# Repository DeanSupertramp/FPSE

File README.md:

# FPSE
Repository per il corso di Fondamenti di Programmazione dei Sistemi Embedded 2020/2021

## Info generali
Su questa repository vengono riportate tutte le attività svolte durante il corso. I progetti/codici prodotti sono stati sviluppati in **STM32CubeIDE**. La scheda di sviluppo utilizzata è la **STM32 Nucleo-F446RE**. Viene inoltre riportato il progetto di fine corso proposto, ovvero un _Self Balancing Robot_.

## Indice degli argomenti
1. [Attività 1 - STM32 Programmazione Base](https://github.com/DeanSupertramp/FPSE/tree/main/Attivit%C3%A01)    
2. [Attività 2 - Digital IO e GPIO](https://github.com/DeanSupertramp/FPSE/tree/main/Attivit%C3%A02) 
3. [Attività 3 - GPIO e Interrupt](https://github.com/DeanSupertramp/FPSE/tree/main/Attivit%C3%A03) 
4. [Attività 4 - IO Analogico](https://github.com/DeanSupertramp/FPSE/tree/main/Attivit%C3%A04) 
5. [Attività 5 - Timers e PWM](https://github.com/DeanSupertramp/FPSE/tree/main/Attivit%C3%A05) 
6. [Attività 6 - Comunicazione Seriale](https://github.com/DeanSupertramp/FPSE/tree/main/Attivit%C3%A06) 
7. [Progetto - Self Balancing Robot](https://github.com/DeanSupertramp/FPSE/tree/main/Progetto) 

<!-- * [License](#license) -->

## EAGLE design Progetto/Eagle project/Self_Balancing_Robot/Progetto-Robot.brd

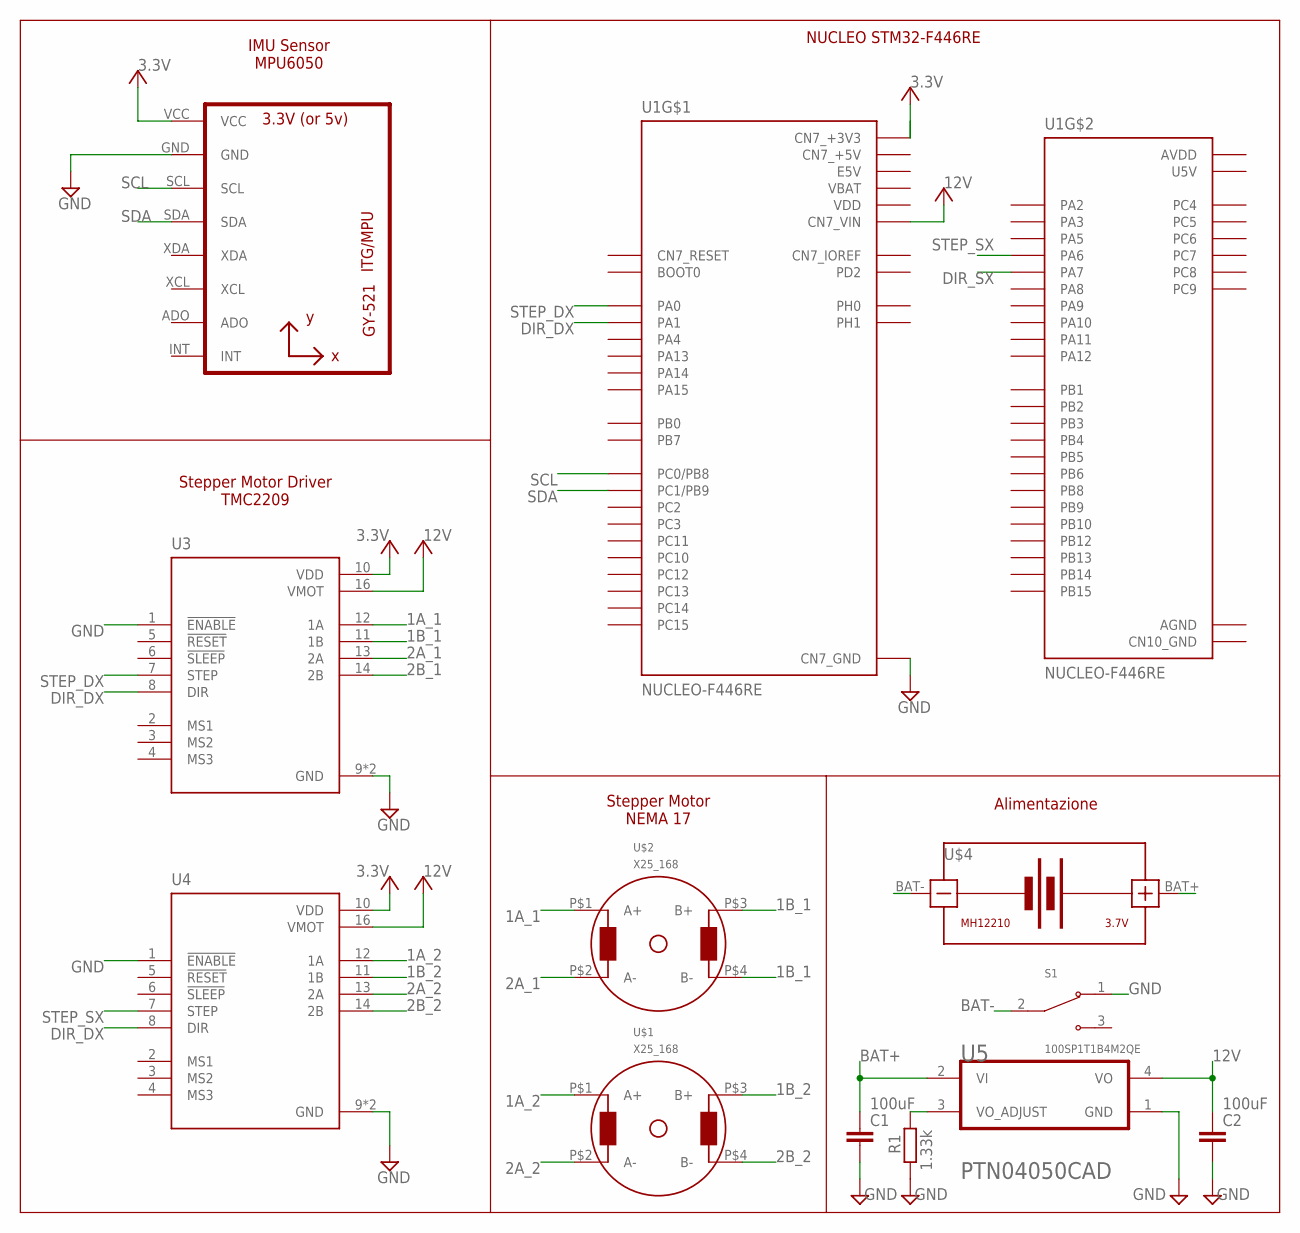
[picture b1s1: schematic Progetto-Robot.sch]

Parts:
C1, C2: 100uF; C050-024X044
R1: 1.33k; 0207/10
S1: 100SP1T1B4M2QE; SW_100SP1T1B4M2QE
U1: NUCLEO-F446RE; MODULE_NUCLEO-F446RE
U2: GY-521MPU6050; GY-521
U3, U4: A4988_STEPPER_MOTOR_DRIVER_CARRIER; MODULE_A4988_STEPPER_MOTOR_DRIVER_CARRIER
U5: TEXAS_INSTRUMENTS_PTN04050CADTEXAS_INSTRUMENTS_PT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; TEXAS_INSTRUMENTS_PTN04050CAD_0
U$1, U$2: X25_168
U$4: BATTERY-LI-MH12210

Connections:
1A_1: U3.12 (1A), U$2.P$1 (A+)
1A_2: U4.12 (1A), U$1.P$1 (A+)
1B_1: U3.11 (1B), U$2.P$3 (B+), U$2.P$4 (B-)
1B_2: U4.11 (1B), U$1.P$3 (B+)
2A_1: U3.13 (2A), U$2.P$2 (A-)
2A_2: U4.13 (2A), U$1.P$2 (A-)
2B_1: U3.14 (2B)
2B_2: U4.14 (2B), U$1.P$4 (B-)
3.3V: U2.VCC, U3.10 (VDD), U4.10 (VDD)
12V: C2.1, U1.CN7_24 (CN7_VIN), U3.16 (VMOT), U4.16 (VMOT), U5.4 (VO)
AGND: U1.CN10_32 (AGND)
AREF: U1.CN5_8 (AREF)
AVDD: U1.CN10_7 (AVDD)
BAT+: C1.1, U5.2 (VI), U$4.BAT+
BAT-: S1.2, U$4.BAT-
CN5_GND: U1.CN5_7 (CN5_GND)
CN6_+3V3: U1.CN6_4 (CN6_+3V3)
CN6_+5V: U1.CN6_5 (CN6_+5V)
CN6_GND: U1.CN6_6 (CN6_GND), U1.CN6_7 (CN6_GND)
CN6_VIN: U1.CN6_8 (CN6_VIN)
CN7_+5V: U1.CN7_18 (CN7_+5V)
CN10_GND: U1.CN10_9 (CN10_GND), U1.CN10_20 (CN10_GND)
DIR_DX: U1.CN7_30 (PA1), U3.8 (DIR), U4.8 (DIR)
DIR_SX: U1.CN10_15 (PA7)
E5V: U1.CN7_6 (E5V)
GND: C1.2, C2.2, R1.1, S1.1, U1.CN7_8 (CN7_GND), U1.CN7_19 (CN7_GND), U1.CN7_20 (CN7_GND), U1.CN7_22 (CN7_GND), U2.GND, U3.1 (!ENABLE), U3.9 (GND), U3.15 (GND), U4.1 (!ENABLE), U4.9 (GND), U4.15 (GND), U5.1 (GND)
unnamed: R1.2, U5.3 (VO_ADJUST)
SCL: U1.CN7_38 (PC0/PB8), U2.SCL
SDA: U1.CN7_36 (PC1/PB9), U2.SDA
STEP_DX: U1.CN7_28 (PA0), U3.7 (STEP)
STEP_SX: U1.CN10_13 (PA6), U4.7 (STEP)
U5V: U1.CN10_8 (U5V)
VBAT: U1.CN7_33 (VBAT)
VDD: U1.CN7_5 (VDD)

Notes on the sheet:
Stepper Motor Driver TMC2209
Stepper Motor NEMA 17
NUCLEO STM32-F446RE
IMU Sensor MPU6050
Alimentazione

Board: 2 copper layers, 12 parts (0 on the bottom side), 20 nets, no tracks yet.

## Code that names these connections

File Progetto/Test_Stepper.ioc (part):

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PH0-OSC_IN.Signal=RCC_OSC_IN
Mcu.UserName=STM32F446RETx
PA14.GPIO_Label=TCK
PA3.GPIOParameters=GPIO_Label
PA6.GPIO_Label=STEP_SX
PC13.GPIO_Label=B1 [Blue PushButton]
PA2.GPIOParameters=GPIO_Label
RCC.SYSCLKSource=RCC_SYSCLKSOURCE_PLLCLK
PA1.GPIO_PuPd=GPIO_PULLDOWN
PH0-OSC_IN.Mode=HSE-External-Oscillator
PA0-WKUP.GPIOParameters=GPIO_Speed,GPIO_PuPd,GPIO_Label
RCC.HSE_VALUE=8000000
PA0-WKUP.GPIO_Speed=GPIO_SPEED_FREQ_HIGH
PA6.GPIO_PuPd=GPIO_PULLUP
PA1.GPIOParameters=GPIO_PuPd,GPIO_Label
PC14-OSC32_IN.Mode=LSE-External-Oscillator
PA14.Mode=Serial_Wire
PB3.GPIOParameters=GPIO_Label
PA13.GPIOParameters=GPIO_Label
PH1-OSC_OUT.Mode=HSE-External-Oscillator
Mcu.Package=LQFP64
PB9.Signal=I2C1_SDA
PA6.Signal=S_TIM3_CH1
PA2.GPIO_Label=USART_TX
PA5.GPIOParameters=GPIO_Label
PA6.GPIO_Speed=GPIO_SPEED_FREQ_HIGH
PA3.Signal=USART2_RX
PB3.GPIO_Label=SWO
PA6.GPIOParameters=GPIO_Speed,GPIO_PuPd,GPIO_Label
PC15-OSC32_OUT.Mode=LSE-External-Oscillator
PC13.Signal=GPXTI13
PC14-OSC32_IN.Signal=RCC_OSC32_IN
boardIOC=true
PA0-WKUP.GPIO_Label=STEP_DX
PA0-WKUP.Signal=S_TIM2_CH1_ETR
PA13.Signal=SYS_JTMS-SWDIO
PA3.Mode=Asynchronous
PB9.Mode=I2C
PC15-OSC32_OUT.Signal=RCC_OSC32_OUT
PA7.GPIO_PuPd=GPIO_PULLDOWN
PA1.Signal=GPIO_Output
PA5.Signal=GPIO_Output
board=NUCLEO-F446RE
PC13.GPIOParameters=GPIO_Label,GPIO_ModeDefaultEXTI
PA1.GPIO_Label=DIR_DX
PH1-OSC_OUT.Signal=RCC_OSC_OUT
PA13.Mode=Serial_Wire
Mcu.Name=STM32F446R(C-E)Tx
PA2.Signal=USART2_TX
PA13.GPIO_Label=TMS
PB3.Signal=SYS_JTDO-SWO
RCC.SYSCLKFreq_VALUE=84000000
PA7.GPIO_Label=DIR_SX
PA5.GPIO_Label=LD2 [Green Led]
PC13.GPIO_ModeDefaultEXTI=GPIO_MODE_IT_FALLING
PA14.GPIOParameters=GPIO_Label
PA14.Signal=SYS_JTCK-SWCLK
PB8.Mode=I2C
PA2.Mode=Asynchronous
PB8.Signal=I2C1_SCL
PA0-WKUP.GPIO_PuPd=GPIO_PULLUP
PA7.GPIOParameters=GPIO_PuPd,GPIO_Label
PA3.GPIO_Label=USART_RX
PA7.Signal=GPIO_Output

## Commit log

2021-05-24 Rename Esercizio 1.md to README.md
2021-05-24 Rename Esercizio 2.md to README.md
2021-06-03 upload Esercizio 1
2021-06-03 upload Esercizio 2
2021-06-03 upload 2 version of Esercizio1
2021-06-22 commit progetto
2021-08-21 add Attività 6 - Esercizio 1
2021-09-16 add matlab+simulink simulation
2021-09-17 add Esp_Robot_Control file
2021-09-17 add Eagle project
2021-09-19 update STM32 project + Presentazione + Relazione
2021-09-19 add SerialRead angle and PID/velocity Matlab files
2021-09-21 update Presentazione e Relazione

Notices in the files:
parts and their libraries:
DIY_libraries: Released under the Creative Commons Attribution 4.0 International License: http://creativecommons.org/licenses/by/4.0
